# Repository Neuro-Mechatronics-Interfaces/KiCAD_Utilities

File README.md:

# KiCAD_Utilities

MATLAB or Python functions/scripts to help with things like electrode coordinate placement etc. on PCB layouts in KiCAD specifically.

## Features

- **Extract coordinates from DXF files**: Parse circular elements (electrodes, mounting holes) from CAD drawings
- **Interactive GUI**: File dialogs and element selection for easy workflow
- **Update KiCad PCB files**: Automatically update footprint locations based on DXF coordinates
- **Coordinate transformations**: Apply offsets, flipping, and centering based on PCB schematic style
- **Flexible element mapping**: Supports multiple element types with configurable metadata

## Python Usage

### Interactive Mode (Recommended)

Run the script and follow the GUI prompts:

```bash
cd python
python example_update_pcb_from_dxf.py
```

The script will guide you through:
1. Selecting a DXF file
2. Selecting a KiCad PCB file
3. Choosing which circular elements to update
4. Configuring coordinate transformations
5. Updating the PCB file

### Requirements

```bash
pip install -r python/requirements.txt
```

Required packages:
- ezdxf
- numpy
- pandas
- matplotlib

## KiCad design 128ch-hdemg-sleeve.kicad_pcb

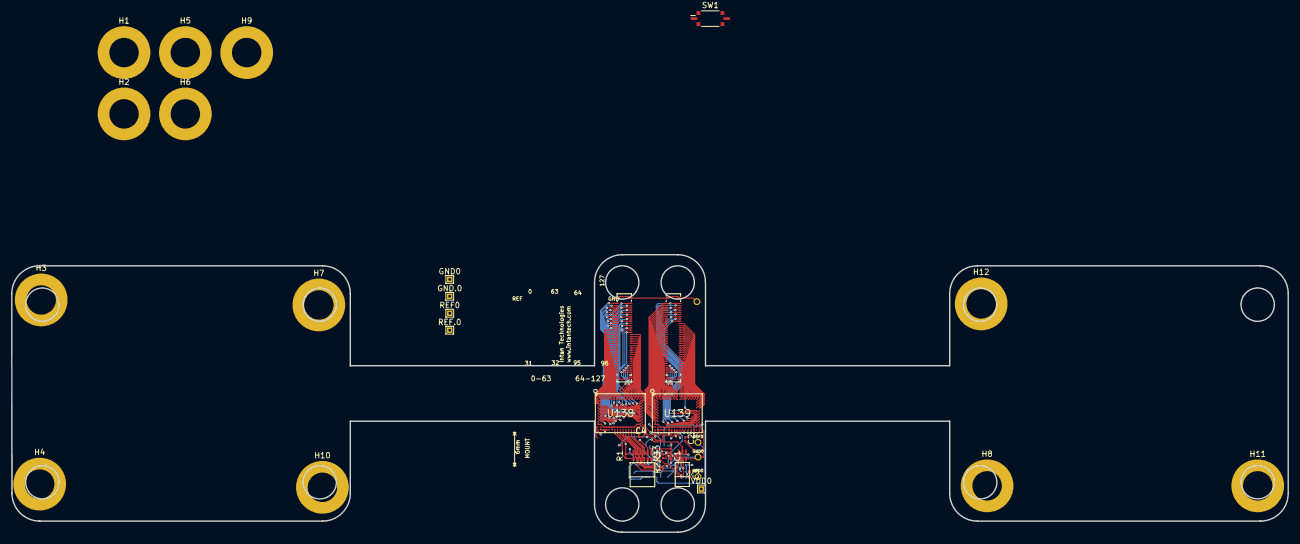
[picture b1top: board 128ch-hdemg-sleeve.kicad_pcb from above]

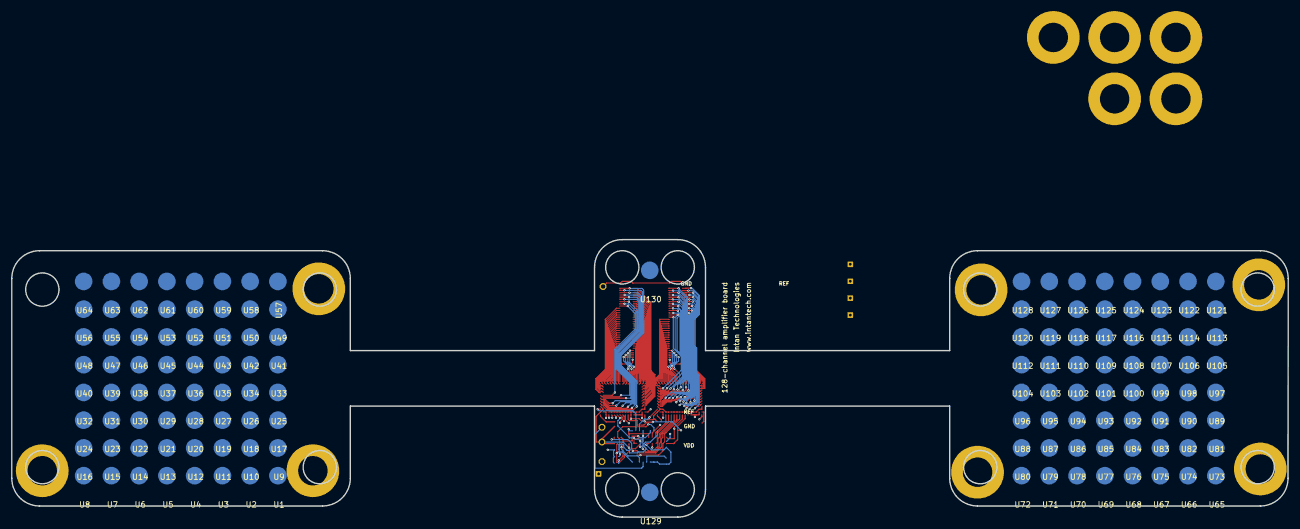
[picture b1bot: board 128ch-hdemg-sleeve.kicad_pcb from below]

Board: 4 copper layers, 230.0 x 50.0 mm, 165 parts (130 on the bottom side), 143 nets.

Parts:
C1, C3: C_0402; C_0402_1005Metric
C2, C4: C_0201; C_0201_0603Metric
GND0, GND.0: TESTPOINT_SMALL; TestPoint_THTPad_1.0x1.0mm_Drill0.5mm
GND0#2, GND.0#2: TESTPOINT_SMALL
H1, H2, H3, H4, H5, H6, H7, H8, H9, H10, H11, H12: MountingHole_Pad; MountingHole_5.3mm_M5_ISO7380_Pad
R1, R2, R3: R_0201; R_0201_0603Metric
REF0, REF.0: TESTPOINT_SMALL; TestPoint_THTPad_1.0x1.0mm_Drill0.5mm
REF0#2: TESTPOINT_SMALL
S1, S2: MOLEX_SLIMSTACK_64
S3: RHD2000-CABLE-AMP-SIDE; OMNETICS_PZN-12-AA
S4: OMNETICS_PZN-06_SMD; OMNETICS_PZN-06-AA
SW1: SW_DIP_x01; SW_DIP_SPSTx01_Slide_Copal_CVS-01xB_W5.9mm_P1mm
U1, U2, U3, U4, U5, U6, U7, U8, U9, U10, U11, U12, U13, U14, U15, U16, U17, U18, U19, U20, U21, U22, U23, U24, U25, U26, U27, U28, U29, U30, U31, U32, U33, U34, U35, U36, U37, U38, U39, U40, U41, U42, U43, U44, U45, U46, U47, U48, U49, U50, U51, U52, U53, U54, U55, U56, U57, U58, U59, U60, U61, U62, U63, U64, U65, U66, U67, U68, U69, U70, U71, U72, U73, U74, U75, U76, U77, U78, U79, U80, U81, U82, U83, U84, U85, U86, U87, U88, U89, U90, U91, U92, U93, U94, U95, U96, U97, U98, U99, U100, U101, U102, U103, U104, U105, U106, U107, U108, U109, U110, U111, U112, U113, U114, U115, U116, U117, U118, U119, U120, U121, U122, U123, U124, U125, U126, U127, U128, U129, U130: 1625-5-57-15_D3.18mm_disk
U138, U139: RHD2164_BGA_BGA; BGA104_9X7
VDD0: TESTPOINT_SMALL
VDD0#2: TESTPOINT_SMALL; TestPoint_THTPad_1.0x1.0mm_Drill0.5mm

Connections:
/RHD2164_128_BGA_1/MISO1+: S3.T4 (MISO1+), U139.N14 (MISO+)
/RHD2164_128_BGA_1/MISO1-: S3.B4 (MISO1-), U139.N13 (MISO-)
CS+: R1.2, S3.T1 (~CS+), U138.N8 (~CS+), U139.N8 (~CS+)
CS-: R1.1, S3.B1 (~CS-), U138.N7 (~CS-), U139.N7 (~CS-)
GND: C1.2, C2.2, C3.2, C4.2, GND0.1, GND0#2.1, GND.0.1, GND.0#2.1, S1.MECH1, S1.MECH2, S1.MECH3, S1.MECH4, S2.MECH1, S2.MECH2, S2.MECH3, S2.MECH4, S3.B6 (GND), S4.B3, SW1.2, U130.1 (OD), U138.M17 (GND1), U138.N1 (GND2), U138.N6 (GND3), U139.M17 (GND1), U139.N1 (GND2), U139.N6 (GND3)
MISO2+: S3.T5 (MISO2+), U138.N14 (MISO+)
MISO2-: S3.B5 (MISO2-), U138.N13 (MISO-)
MOSI+: R3.2, S3.T3 (MOSI+), U138.N12 (MOSI+), U139.N12 (MOSI+)
MOSI-: R3.1, S3.B3 (MOSI-), U138.N11 (MOSI-), U139.N11 (MOSI-)
unnamed: U1.1 (OD), U139.K2 (IN0)
unnamed: U10.1 (OD), U139.E1 (IN9)
unnamed: U11.1 (OD), U139.E2 (IN10)
unnamed: U12.1 (OD), U139.D1 (IN11)
unnamed: U13.1 (OD), U139.D2 (IN12)
unnamed: U100.1 (OD), U138.A11 (IN35)
unnamed: U101.1 (OD), U138.B11 (IN36)
unnamed: U102.1 (OD), U138.A12 (IN37)
unnamed: U103.1 (OD), U138.B12 (IN38)
unnamed: U104.1 (OD), U138.A13 (IN39)
unnamed: U105.1 (OD), U138.B13 (IN40)
unnamed: U106.1 (OD), U138.A14 (IN41)
unnamed: U107.1 (OD), U138.B14 (IN42)
unnamed: U108.1 (OD), U138.A15 (IN43)
unnamed: U109.1 (OD), U138.B15 (IN44)
unnamed: U110.1 (OD), U138.A16 (IN45)
unnamed: U111.1 (OD), U138.B16 (IN46)
unnamed: U112.1 (OD), U138.A17 (IN47)
unnamed: U113.1 (OD), U138.B17 (IN48)
unnamed: U114.1 (OD), U138.C16 (IN49)
unnamed: U115.1 (OD), U138.C17 (IN50)
unnamed: U116.1 (OD), U138.D16 (IN51)
unnamed: U117.1 (OD), U138.D17 (IN52)
unnamed: U118.1 (OD), U138.E16 (IN53)
unnamed: U119.1 (OD), U138.E17 (IN54)
unnamed: U120.1 (OD), U138.F16 (IN55)
unnamed: U121.1 (OD), U138.F17 (IN56)
unnamed: U122.1 (OD), U138.G16 (IN57)
unnamed: U123.1 (OD), U138.G17 (IN58)
unnamed: U124.1 (OD), U138.H16 (IN59)
unnamed: U125.1 (OD), U138.H17 (IN60)
unnamed: U126.1 (OD), U138.J16 (IN61)
unnamed: U127.1 (OD), U138.J17 (IN62)
unnamed: U128.1 (OD), U138.K16 (IN63)
unnamed: C4.1, U138.N17 (ADC_REF)
unnamed: U65.1 (OD), U138.K2 (IN0)
unnamed: U66.1 (OD), U138.J1 (IN1)
unnamed: U67.1 (OD), U138.J2 (IN2)
unnamed: U68.1 (OD), U138.H1 (IN3)
unnamed: U69.1 (OD), U138.H2 (IN4)
unnamed: U70.1 (OD), U138.G1 (IN5)
unnamed: U71.1 (OD), U138.G2 (IN6)
unnamed: U72.1 (OD), U138.F1 (IN7)
unnamed: U73.1 (OD), U138.F2 (IN8)
unnamed: U74.1 (OD), U138.E1 (IN9)
unnamed: U75.1 (OD), U138.E2 (IN10)
unnamed: U76.1 (OD), U138.D1 (IN11)
unnamed: U77.1 (OD), U138.D2 (IN12)
unnamed: U78.1 (OD), U138.C1 (IN13)
unnamed: U79.1 (OD), U138.C2 (IN14)
unnamed: U80.1 (OD), U138.B1 (IN15)
unnamed: U81.1 (OD), U138.A1 (IN16)
unnamed: U82.1 (OD), U138.B2 (IN17)
unnamed: U83.1 (OD), U138.A2 (IN18)
unnamed: U84.1 (OD), U138.B3 (IN19)
unnamed: U85.1 (OD), U138.A3 (IN20)
unnamed: U86.1 (OD), U138.B4 (IN21)
unnamed: U87.1 (OD), U138.A4 (IN22)
unnamed: U88.1 (OD), U138.B5 (IN23)
unnamed: U89.1 (OD), U138.A5 (IN24)
unnamed: U90.1 (OD), U138.B6 (IN25)
unnamed: U91.1 (OD), U138.A6 (IN26)
unnamed: U92.1 (OD), U138.B7 (IN27)
unnamed: U93.1 (OD), U138.A7 (IN28)
unnamed: U94.1 (OD), U138.B8 (IN29)
unnamed: U95.1 (OD), U138.A8 (IN30)
unnamed: U96.1 (OD), U138.B9 (IN31)
unnamed: U97.1 (OD), U138.A9 (IN32)
unnamed: U98.1 (OD), U138.A10 (IN33)
unnamed: U99.1 (OD), U138.B10 (IN34)
unnamed: C2.1, U139.N17 (ADC_REF)
unnamed: U2.1 (OD), U139.J1 (IN1)
unnamed: U3.1 (OD), U139.J2 (IN2)
unnamed: U4.1 (OD), U139.H1 (IN3)
unnamed: U5.1 (OD), U139.H2 (IN4)
unnamed: U6.1 (OD), U139.G1 (IN5)
unnamed: U7.1 (OD), U139.G2 (IN6)
unnamed: U8.1 (OD), U139.F1 (IN7)
unnamed: U9.1 (OD), U139.F2 (IN8)
unnamed: U14.1 (OD), U139.C1 (IN13)
unnamed: U15.1 (OD), U139.C2 (IN14)
unnamed: U16.1 (OD), U139.B1 (IN15)
unnamed: U17.1 (OD), U139.A1 (IN16)
unnamed: U18.1 (OD), U139.B2 (IN17)
unnamed: U19.1 (OD), U139.A2 (IN18)
unnamed: U20.1 (OD), U139.B3 (IN19)
unnamed: U21.1 (OD), U139.A3 (IN20)
unnamed: U22.1 (OD), U139.B4 (IN21)
unnamed: U23.1 (OD), U139.A4 (IN22)
unnamed: U24.1 (OD), U139.B5 (IN23)
unnamed: U25.1 (OD), U139.A5 (IN24)
unnamed: U26.1 (OD), U139.B6 (IN25)
unnamed: U27.1 (OD), U139.A6 (IN26)
unnamed: U28.1 (OD), U139.B7 (IN27)
unnamed: U29.1 (OD), U139.A7 (IN28)
unnamed: U30.1 (OD), U139.B8 (IN29)
unnamed: U31.1 (OD), U139.A8 (IN30)
unnamed: U32.1 (OD), U139.B9 (IN31)
unnamed: U33.1 (OD), U139.A9 (IN32)
unnamed: U34.1 (OD), U139.A10 (IN33)
unnamed: U35.1 (OD), U139.B10 (IN34)
unnamed: U36.1 (OD), U139.A11 (IN35)
unnamed: U37.1 (OD), U139.B11 (IN36)
unnamed: U38.1 (OD), U139.A12 (IN37)
unnamed: U39.1 (OD), U139.B12 (IN38)
unnamed: U40.1 (OD), U139.A13 (IN39)
unnamed: U41.1 (OD), U139.B13 (IN40)
unnamed: U42.1 (OD), U139.A14 (IN41)
unnamed: U43.1 (OD), U139.B14 (IN42)
unnamed: U44.1 (OD), U139.A15 (IN43)
unnamed: U45.1 (OD), U139.B15 (IN44)
unnamed: U46.1 (OD), U139.A16 (IN45)
unnamed: U47.1 (OD), U139.B16 (IN46)
unnamed: U48.1 (OD), U139.A17 (IN47)
unnamed: U49.1 (OD), U139.B17 (IN48)
unnamed: U50.1 (OD), U139.C16 (IN49)
unnamed: U51.1 (OD), U139.C17 (IN50)
unnamed: U52.1 (OD), U139.D16 (IN51)
unnamed: U53.1 (OD), U139.D17 (IN52)
unnamed: U54.1 (OD), U139.E16 (IN53)
unnamed: U55.1 (OD), U139.E17 (IN54)
unnamed: U56.1 (OD), U139.F16 (IN55)
unnamed: U57.1 (OD), U139.F17 (IN56)
unnamed: U58.1 (OD), U139.G16 (IN57)
unnamed: U59.1 (OD), U139.G17 (IN58)
unnamed: U60.1 (OD), U139.H16 (IN59)
unnamed: U61.1 (OD), U139.H17 (IN60)
unnamed: U62.1 (OD), U139.J16 (IN61)
unnamed: U63.1 (OD), U139.J17 (IN62)
unnamed: U64.1 (OD), U139.K16 (IN63)
REF: REF0.1, REF0#2.1, REF.0.1, SW1.1, U129.1 (OD), U138.M1 (REF_ELEC), U139.M1 (REF_ELEC)
SCLK+: R2.2, S3.T2 (SCLK+), U138.N10 (SCLK+), U139.N10 (SCLK+)
SCLK-: R2.1, S3.B2 (SCLK-), U138.N9 (SCLK-), U139.N9 (SCLK-)
VCC: C1.1, C3.1, S3.T6 (VDD), U138.M2 (VESD), U138.M15 (VDD1), U138.M16 (LVDS_EN), U138.N2 (VDD2), U138.N3 (AUXIN1), U138.N4 (AUXIN2), U138.N5 (AUXIN3), U138.N15 (VDD3), U139.M2 (VESD), U139.M15 (VDD1), U139.M16 (LVDS_EN), U139.N2 (VDD2), U139.N3 (AUXIN1), U139.N4 (AUXIN2), U139.N5 (AUXIN3), U139.N15 (VDD3), VDD0.1, VDD0#2.1

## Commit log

2024-06-21 Adds first version that parses DXF
2024-06-21 Adds .kicad_pcb to gitignore. Add to example indicating export step.
2024-06-21 Fixed incorrect leading filter string
    (had incorrect ')' at end of line for matching footprint)
2024-06-25 Added Python example and support
2024-09-10 updating remote repo
2025-01-25 updated for better parsing of unique entities
2025-02-28 Tweaks to upport schematic centering
2025-12-10 interactive
2025-12-11 Refactor: Add interactive GUI for PCB update from DXF
    - Add file selection dialogs for DXF and PCB files
    - Add interactive element selection from detected circles
    - Add coordinate transformation configuration dialogs
    - Add automatic footprint discovery from PCB files
    - Fix 6mm-electrode footprint name
    - Improve error handling and user feedback
